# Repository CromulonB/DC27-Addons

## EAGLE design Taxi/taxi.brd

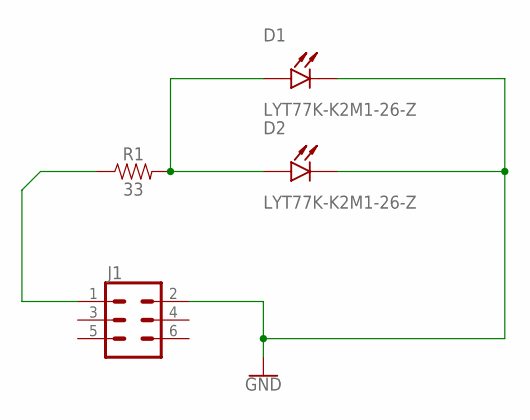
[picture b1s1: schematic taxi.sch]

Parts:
D1, D2: LYT77K-K2M1-26-Z; LED_LYT77K-K2M1-26-Z
J1: CONN_03X2SHROUD; 2X3-SHROUDED
R1: 33; 0603

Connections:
GND: D1.1 (C), D2.1 (C), J1.2
unnamed: J1.1, R1.1
unnamed: D1.2 (A), D2.2 (A), R1.2

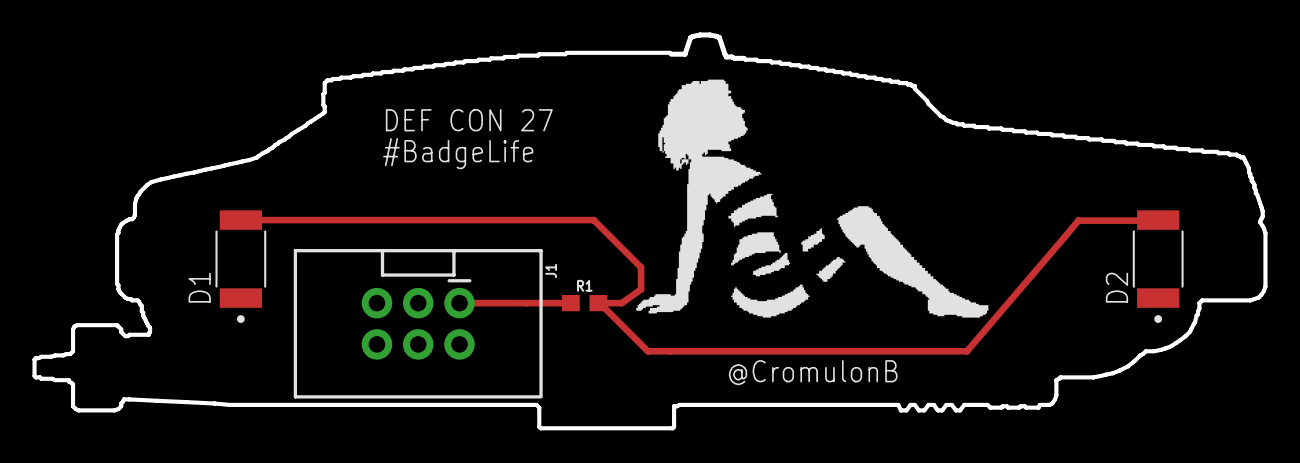
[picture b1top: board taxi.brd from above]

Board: 2 copper layers, 75.7 x 24.2 mm, 4 parts (0 on the bottom side), 3 nets.

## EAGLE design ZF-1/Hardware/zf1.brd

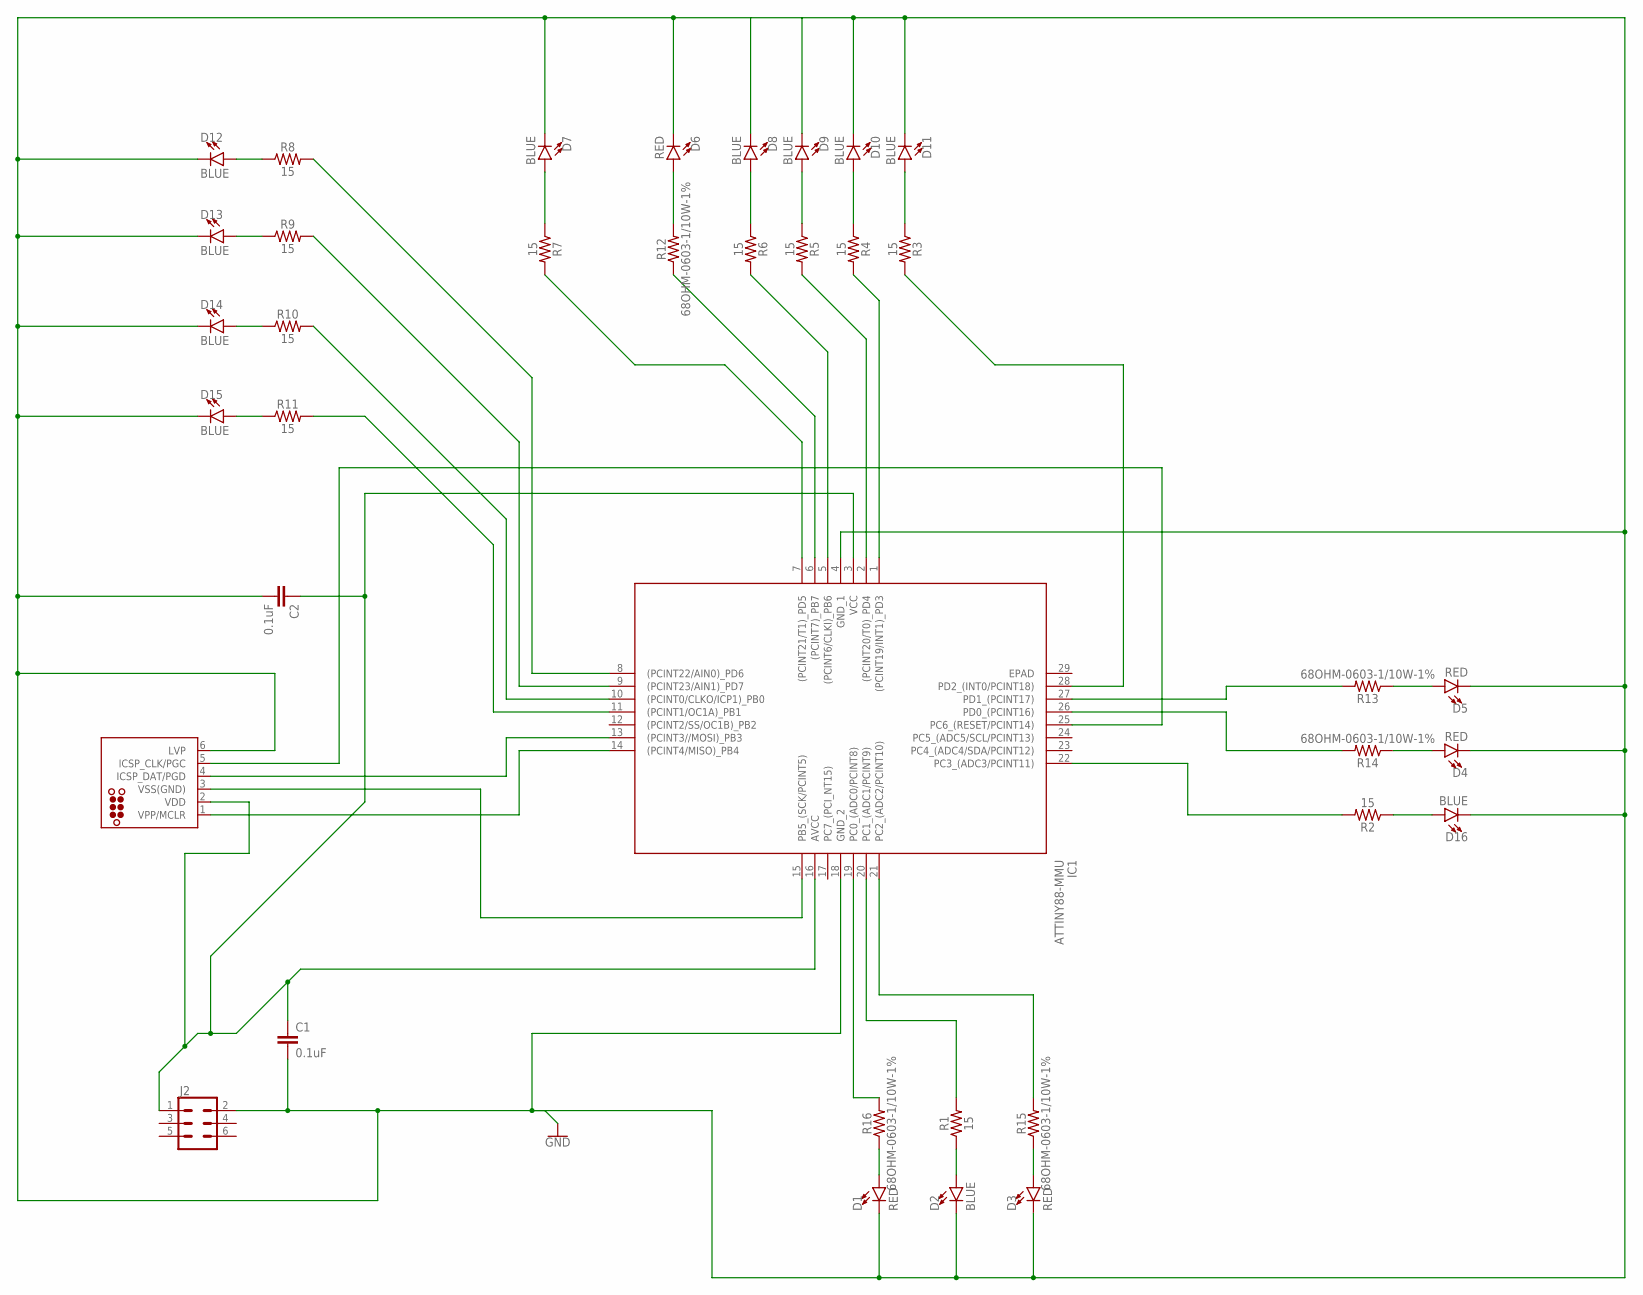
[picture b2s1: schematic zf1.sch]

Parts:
C1, C2: 0.1uF; 0603
D1, D3, D4, D5, D6: RED; LED-0603
D2, D7, D8, D9, D10, D11, D12, D13, D14, D15, D16: BLUE; LED-0603
IC1: ATTINY88-MMU; QFN45P400X400X100-29N
J1: TC2030-MCP-NL
J2: CONN_03X2SHROUD; 2X3-SHROUDED
R1, R2, R3, R4, R5, R6, R7, R8, R9, R10, R11: 15; 0603
R12, R13, R14, R15, R16: 68OHM-0603-1/10W-1%; 0603

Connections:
GND: C1.2, C2.2, D1.C, D2.C, D3.C, D4.C, D5.C, D6.C, D7.C, D8.C, D9.C, D10.C, D11.C, D12.C, D13.C, D14.C, D15.C, D16.C, IC1.4 (GND_1), IC1.18 (GND_2), J1.6 (LVP), J2.2
unnamed: C1.1, C2.1, IC1.3 (VCC), IC1.16 (AVCC), J1.2 (VDD), J2.1
unnamed: D15.A, R11.1
unnamed: IC1.13 ((PCINT3//MOSI)_PB3), J1.4 (ICSP_DAT/PGD)
unnamed: IC1.14 ((PCINT4/MISO)_PB4), J1.1 (VPP/MCLR)
unnamed: IC1.15 (PB5_(SCK/PCINT5)), J1.3 (VSS(GND))
unnamed: D14.A, R10.1
unnamed: IC1.25 (PC6_(RESET/PCINT14)), J1.5 (ICSP_CLK/PGC)
unnamed: D13.A, R9.1
unnamed: D12.A, R8.1
unnamed: D7.A, R7.1
unnamed: D6.A, R12.2
unnamed: D8.A, R6.1
unnamed: D9.A, R5.1
unnamed: D10.A, R4.1
unnamed: D11.A, R3.1
unnamed: D5.A, R13.1
unnamed: D4.A, R14.1
unnamed: D16.A, R2.1
unnamed: D3.A, R15.1
unnamed: D2.A, R1.1
unnamed: D1.A, R16.1
unnamed: IC1.19 (PC0_(ADC0/PCINT8)), R16.2
unnamed: IC1.20 (PC1_(ADC1/PCINT9)), R1.2
unnamed: IC1.21 (PC2_(ADC2/PCINT10)), R15.2
unnamed: IC1.22 (PC3_(ADC3/PCINT11)), R2.2
unnamed: IC1.26 (PD0_(PCINT16)), R14.2
unnamed: IC1.27 (PD1_(PCINT17)), R13.2
unnamed: IC1.28 (PD2_(INT0/PCINT18)), R3.2
unnamed: IC1.1 ((PCINT19/INT1)_PD3), R4.2
unnamed: IC1.2 ((PCINT20/T0)_PD4), R5.2
unnamed: IC1.5 ((PCINT6/CLKI)_PB6), R6.2
unnamed: IC1.6 ((PCINT7)_PB7), R12.1
unnamed: IC1.7 ((PCINT21/T1)_PD5), R7.2
unnamed: IC1.8 ((PCINT22/AIN0)_PD6), R8.2
unnamed: IC1.9 ((PCINT23/AIN1)_PD7), R9.2
unnamed: IC1.10 ((PCINT0/CLKO/ICP1)_PB0), R10.2
unnamed: IC1.11 ((PCINT1/OC1A)_PB1), R11.2

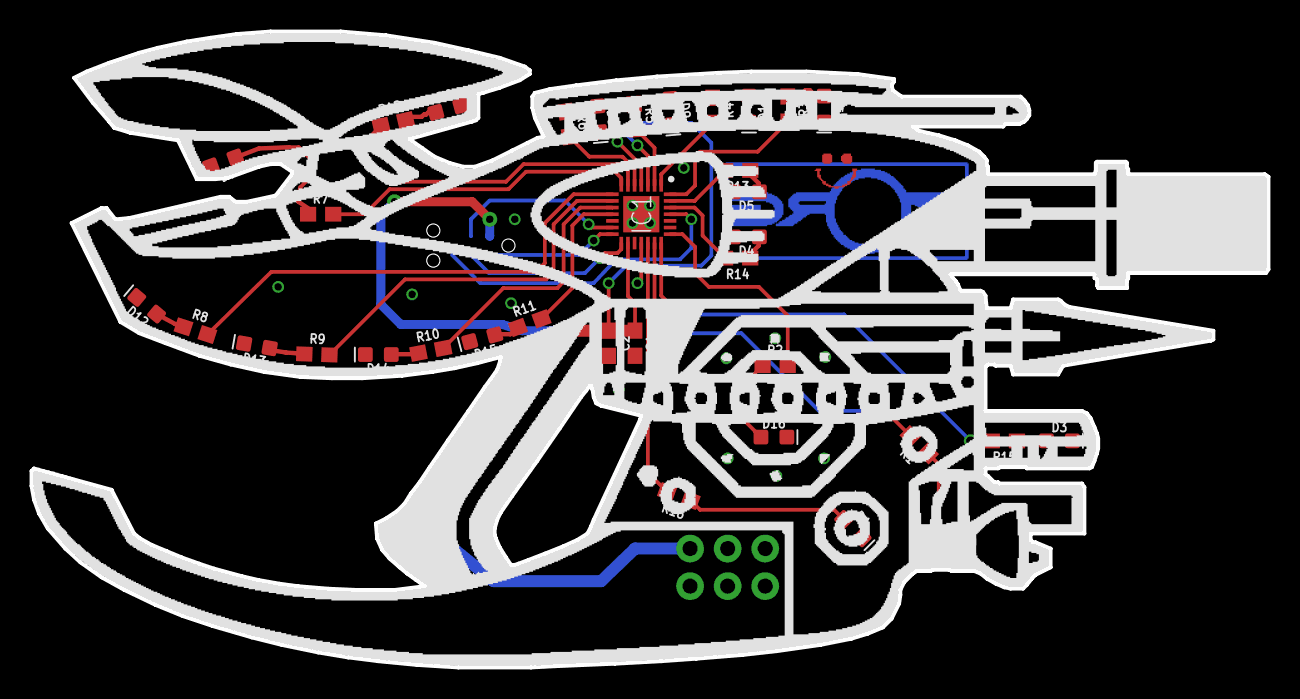
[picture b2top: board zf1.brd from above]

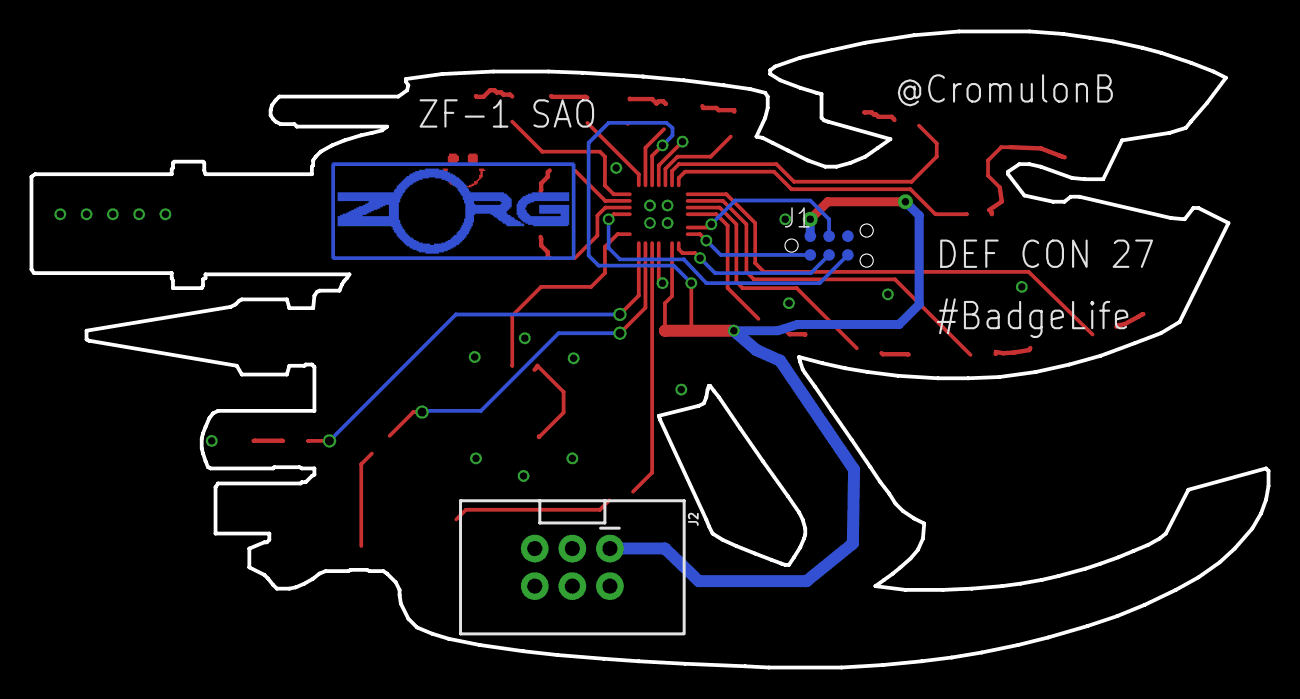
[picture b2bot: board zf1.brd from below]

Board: 2 copper layers, 83.6 x 43.0 mm, 37 parts (2 on the bottom side), 38 nets.

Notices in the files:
parts and their libraries:
SparkFun-Connectors: Licensing: Creative Commons ShareAlike 4.0 International - https://creativecommons.org/licenses/by-sa/4.0
tag-connect: ©2009 ROFA.cz - modified and updated by Robert Darlington ‹rdarlington@gmail.com›
